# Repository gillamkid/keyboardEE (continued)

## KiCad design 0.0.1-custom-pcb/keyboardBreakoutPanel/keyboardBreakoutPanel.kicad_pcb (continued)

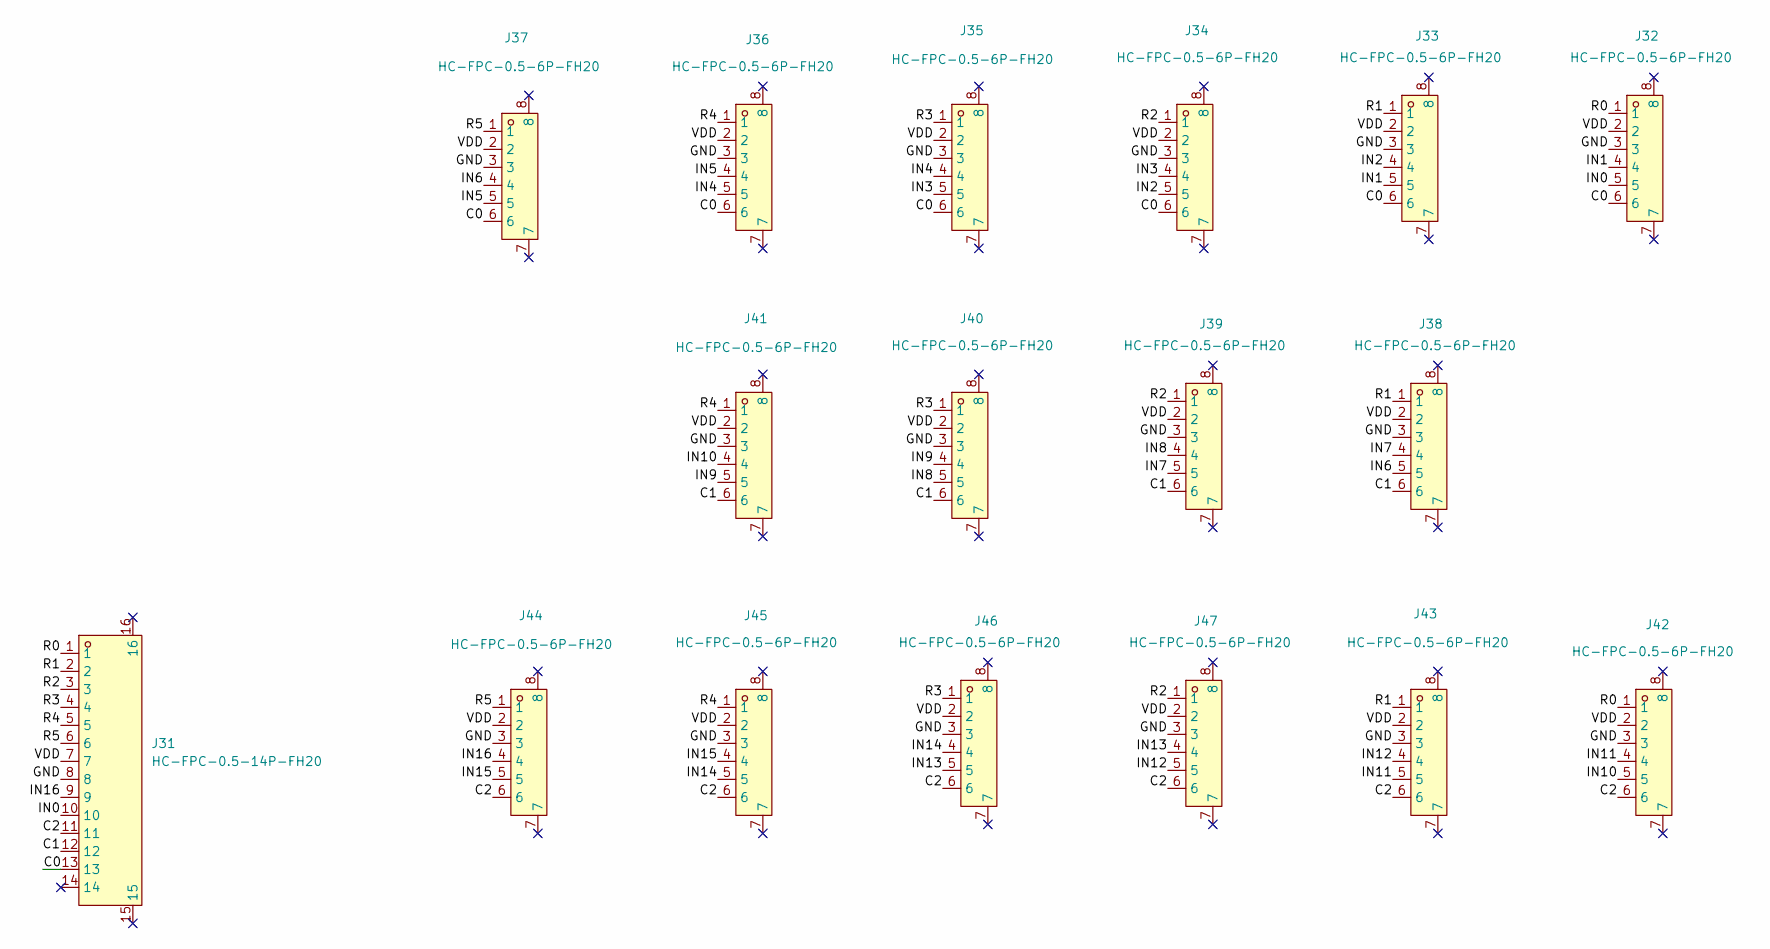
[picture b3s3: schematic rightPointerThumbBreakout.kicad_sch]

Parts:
J31: HC-FPC-0.5-14P-FH20; FPC-SMD_14P-P0.50_HC-FPC-0.5-14P-FH20; MPN HC-FPC-0.5-14P-FH20; LCSC Part C19273929
J32, J33, J34, J35, J36, J37, J38, J39, J40, J41, J42, J43, J44, J45, J46, J47: HC-FPC-0.5-6P-FH20; FPC-SMD_6P-P0.50_HC-FPC-0.5-6P-FH20; MPN HC-FPC-0.5-6P-FH20; LCSC Part C19273925

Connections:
/rightPointerThumbBreakout/C0: J31.13, J32.6, J33.6, J34.6, J35.6, J36.6, J37.6
/rightPointerThumbBreakout/C1: J31.12, J38.6, J39.6, J40.6, J41.6
/rightPointerThumbBreakout/C2: J31.11, J42.6, J43.6, J44.6, J45.6, J46.6, J47.6
/rightPointerThumbBreakout/GND: J31.8, J32.3, J33.3, J34.3, J35.3, J36.3, J37.3, J38.3, J39.3, J40.3, J41.3, J42.3, J43.3, J44.3, J45.3, J46.3, J47.3
/rightPointerThumbBreakout/IN0: J31.10, J32.5
/rightPointerThumbBreakout/IN1: J32.4, J33.5
/rightPointerThumbBreakout/IN2: J33.4, J34.5
/rightPointerThumbBreakout/IN3: J34.4, J35.5
/rightPointerThumbBreakout/IN4: J35.4, J36.5
/rightPointerThumbBreakout/IN5: J36.4, J37.5
/rightPointerThumbBreakout/IN6: J37.4, J38.5
/rightPointerThumbBreakout/IN7: J38.4, J39.5
/rightPointerThumbBreakout/IN8: J39.4, J40.5
/rightPointerThumbBreakout/IN9: J40.4, J41.5
/rightPointerThumbBreakout/IN10: J41.4, J42.5
/rightPointerThumbBreakout/IN11: J42.4, J43.5
/rightPointerThumbBreakout/IN12: J43.4, J47.5
/rightPointerThumbBreakout/IN13: J46.5, J47.4
/rightPointerThumbBreakout/IN14: J45.5, J46.4
/rightPointerThumbBreakout/IN15: J44.5, J45.4
/rightPointerThumbBreakout/IN16: J31.9, J44.4
/rightPointerThumbBreakout/R0: J31.1, J32.1, J42.1
/rightPointerThumbBreakout/R1: J31.2, J33.1, J38.1, J43.1
/rightPointerThumbBreakout/R2: J31.3, J34.1, J39.1, J47.1
/rightPointerThumbBreakout/R3: J31.4, J35.1, J40.1, J46.1
/rightPointerThumbBreakout/R4: J31.5, J36.1, J41.1, J45.1
/rightPointerThumbBreakout/R5: J31.6, J37.1, J44.1
/rightPointerThumbBreakout/VDD: J31.7, J32.2, J33.2, J34.2, J35.2, J36.2, J37.2, J38.2, J39.2, J40.2, J41.2, J42.2, J43.2, J44.2, J45.2, J46.2, J47.2

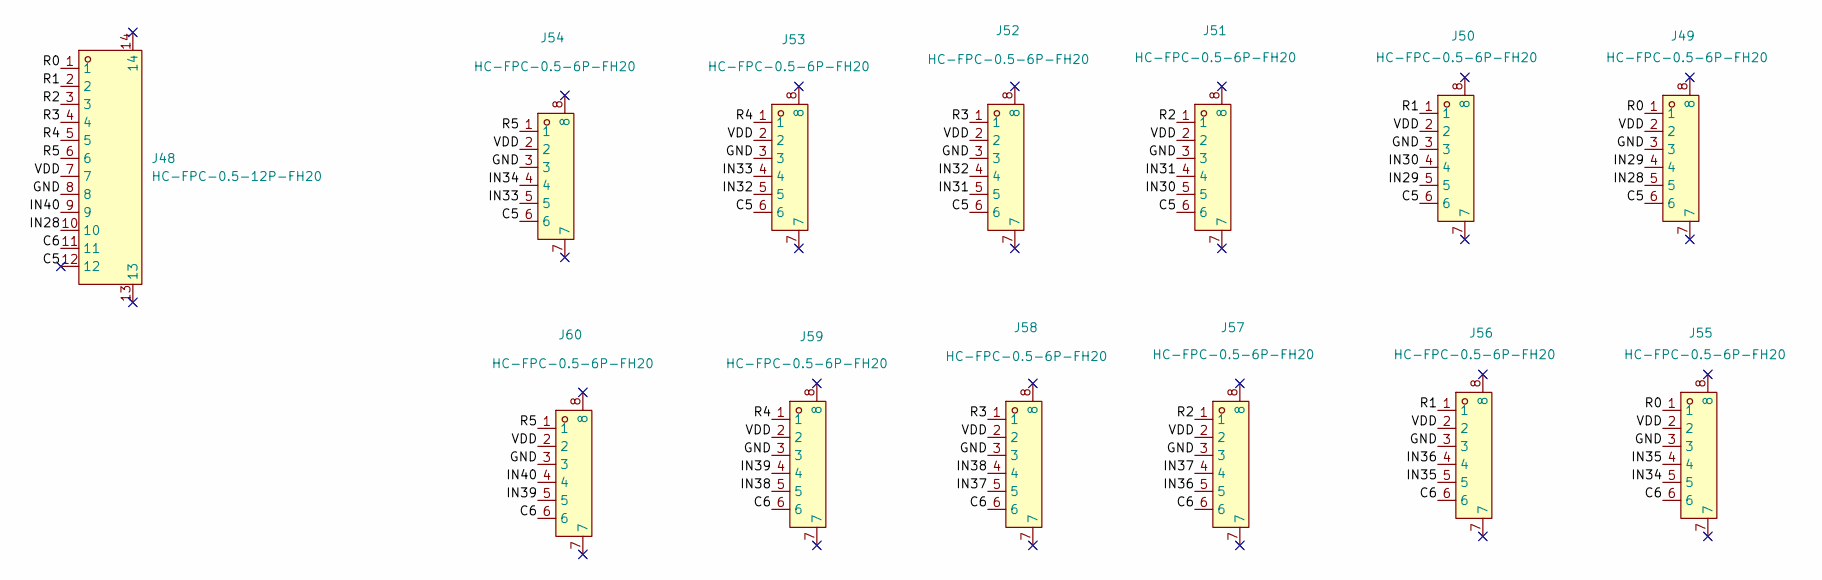
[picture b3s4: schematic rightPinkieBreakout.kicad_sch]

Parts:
J48: HC-FPC-0.5-12P-FH20; FPC-SMD_12P-P0.50_HC-FPC-0.5-12P-FH20; MPN HC-FPC-0.5-12P-FH20; LCSC Part C19273928
J49, J50, J51, J52, J53, J54, J55, J56, J57, J58, J59, J60: HC-FPC-0.5-6P-FH20; FPC-SMD_6P-P0.50_HC-FPC-0.5-6P-FH20; MPN HC-FPC-0.5-6P-FH20; LCSC Part C19273925

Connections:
/rightPinkieBreakout/C5: J48.12, J49.6, J50.6, J51.6, J52.6, J53.6, J54.6
/rightPinkieBreakout/C6: J48.11, J55.6, J56.6, J57.6, J58.6, J59.6, J60.6
/rightPinkieBreakout/GND: J48.8, J49.3, J50.3, J51.3, J52.3, J53.3, J54.3, J55.3, J56.3, J57.3, J58.3, J59.3, J60.3
/rightPinkieBreakout/IN28: J48.10, J49.5
/rightPinkieBreakout/IN29: J49.4, J50.5
/rightPinkieBreakout/IN30: J50.4, J51.5
/rightPinkieBreakout/IN31: J51.4, J52.5
/rightPinkieBreakout/IN32: J52.4, J53.5
/rightPinkieBreakout/IN33: J53.4, J54.5
/rightPinkieBreakout/IN34: J54.4, J55.5
/rightPinkieBreakout/IN35: J55.4, J56.5
/rightPinkieBreakout/IN36: J56.4, J57.5
/rightPinkieBreakout/IN37: J57.4, J58.5
/rightPinkieBreakout/IN38: J58.4, J59.5
/rightPinkieBreakout/IN39: J59.4, J60.5
/rightPinkieBreakout/IN40: J48.9, J60.4
/rightPinkieBreakout/R0: J48.1, J49.1, J55.1
/rightPinkieBreakout/R1: J48.2, J50.1, J56.1
/rightPinkieBreakout/R2: J48.3, J51.1, J57.1
/rightPinkieBreakout/R3: J48.4, J52.1, J58.1
/rightPinkieBreakout/R4: J48.5, J53.1, J59.1
/rightPinkieBreakout/R5: J48.6, J54.1, J60.1
/rightPinkieBreakout/VDD: J48.7, J49.2, J50.2, J51.2, J52.2, J53.2, J54.2, J55.2, J56.2, J57.2, J58.2, J59.2, J60.2

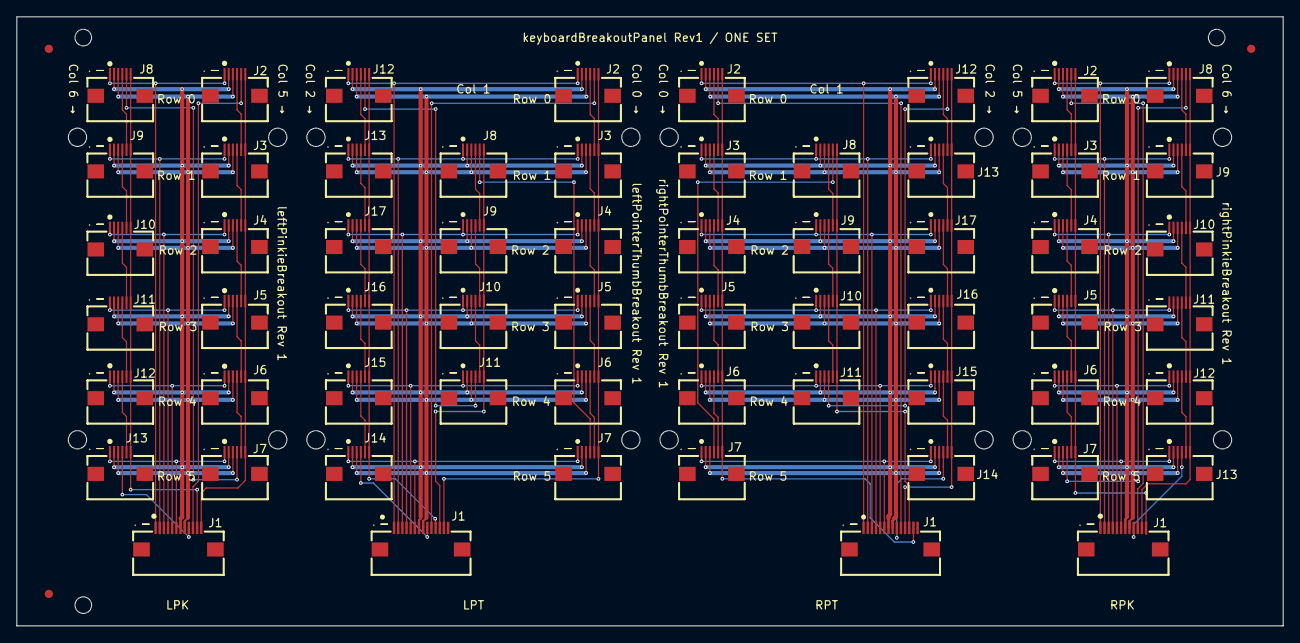
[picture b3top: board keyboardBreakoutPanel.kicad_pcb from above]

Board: 2 copper layers, 152.4 x 73.3 mm, 82 parts (0 on the bottom side), 102 nets.

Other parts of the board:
FID1, FID2, FID3: Fiducial; Fiducial_1mm
H1, H2, H3, H4, H5, H6, H7, H8, H9, H10, H11, H12, H13, H14, H15, H16: MountingHole_2.2mm_M2_4.4mmHead
TOOL1, TOOL2, TOOL3: Tooling hole; ToolingHole_2mm

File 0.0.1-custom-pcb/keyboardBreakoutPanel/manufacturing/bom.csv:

Comment,Designator,Footprint,LCSC,Quantity
HC-FPC-0.5-12P-FH20,"J1,J48",FPC-SMD_12P-P0.50_HC-FPC-0.5-12P-FH20,C19273928,2
HC-FPC-0.5-6P-FH20,"J2,J3,J4,J5,J6,J7,J8,J9,J10,J11,J12,J13,J15,J16,J17,J18,J19,J20,J21,J22,J23,J24,J25,J26,J27,J28,J29,J30,J32,J33,J34,J35,J36,J37,J38,J39,J40,J41,J42,J43,J44,J45,J46,J47,J49,J50,J51,J52,J53,J54,J55,J56,J57,J58,J59,J60",FPC-SMD_6P-P0.50_HC-FPC-0.5-6P-FH20,C19273925,56
HC-FPC-0.5-14P-FH20,"J14,J31",FPC-SMD_14P-P0.50_HC-FPC-0.5-14P-FH20,C19273929,2

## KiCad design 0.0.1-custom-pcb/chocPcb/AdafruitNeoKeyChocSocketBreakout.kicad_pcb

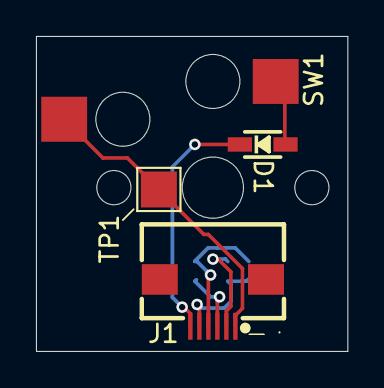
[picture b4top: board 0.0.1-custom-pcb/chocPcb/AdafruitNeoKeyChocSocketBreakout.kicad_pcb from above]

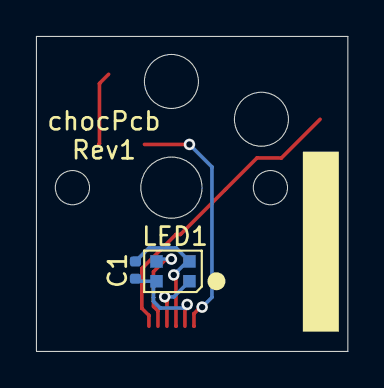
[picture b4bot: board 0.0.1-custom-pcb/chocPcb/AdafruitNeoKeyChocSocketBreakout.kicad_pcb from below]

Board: 2 copper layers, 17.3 x 17.5 mm, 6 parts (2 on the bottom side), 7 nets.

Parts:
C1: 100nF; C_0402_1005Metric
D1: 1N4148WS; SOD-323
J1: HC-FPC-0.5-6P-FH20; FPC-SMD_6P-P0.50_HC-FPC-0.5-6P-FH20
LED1: WS2812B-2020; LED_WS2812B-2020_PLCC4_2.0x2.0mm
SW1: Kailh Choc socket; KAILH_CHOC_SOCKET
TP1: TestPoint_Pad_2.0x2.0mm

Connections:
GND: C1.2, J1.4, LED1.2
unnamed: D1.A, SW1.1
NEO_IN: J1.2, LED1.3
NEO_OUT: J1.3, LED1.1
SWITCHA: J1.1, SW1.2, TP1.1
SWITCHC: D1.C, J1.6
VDD: C1.1, J1.5, LED1.4

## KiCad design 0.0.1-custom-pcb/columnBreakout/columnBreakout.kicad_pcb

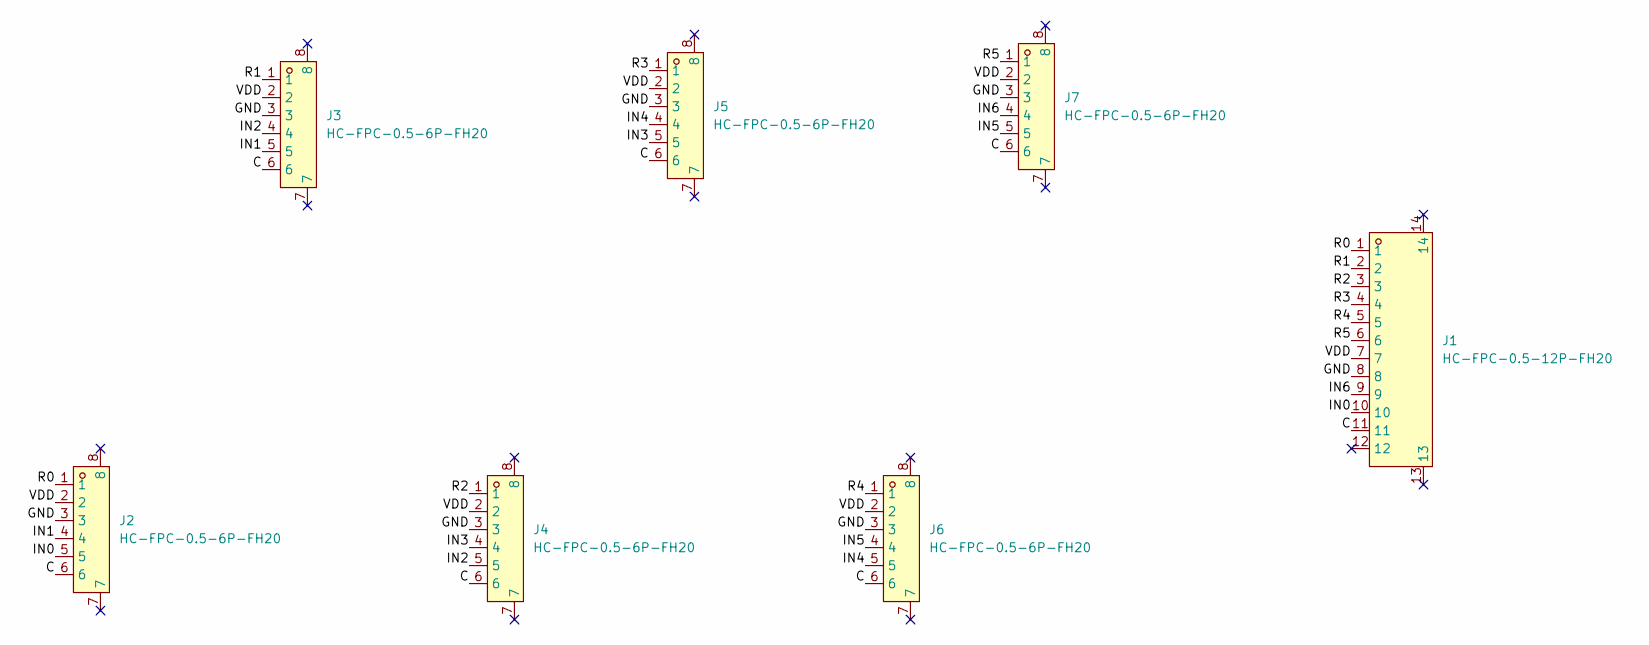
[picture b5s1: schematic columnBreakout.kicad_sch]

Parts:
J1: HC-FPC-0.5-12P-FH20; FPC-SMD_12P-P0.50_HC-FPC-0.5-12P-FH20; MPN HC-FPC-0.5-12P-FH20; LCSC Part C19273928
J2, J3, J4, J5, J6, J7: HC-FPC-0.5-6P-FH20; FPC-SMD_6P-P0.50_HC-FPC-0.5-6P-FH20; MPN HC-FPC-0.5-6P-FH20; LCSC Part C19273925

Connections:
/C: J1.11 (R1), J2.6 (VDD), J3.6 (VDD), J4.6 (VDD), J5.6 (VDD), J6.6 (VDD), J7.6 (VDD)
/GND: J1.8 (R4), J2.3 (IN0), J3.3 (IN1), J4.3 (IN2), J5.3 (IN3), J6.3 (IN4), J7.3 (IN5)
/IN0: J1.10 (R2), J2.5 (GND)
/IN1: J2.4 (IN1), J3.5 (GND)
/IN2: J3.4 (IN2), J4.5 (GND)
/IN3: J4.4 (IN3), J5.5 (GND)
/IN4: J5.4 (IN4), J6.5 (GND)
/IN5: J6.4 (IN5), J7.5 (GND)
/IN6: J1.9 (R3), J7.4 (IN6)
/R0: J1.1, J2.1 (R0)
/R1: J1.2 (C), J3.1 (R1)
/R2: J1.3 (IN0), J4.1 (R2)
/R3: J1.4 (IN6), J5.1 (R3)
/R4: J1.5 (GND), J6.1 (R4)
/R5: J1.6 (VDD), J7.1 (R5)
/VDD: J1.7 (R5), J2.2 (C), J3.2 (C), J4.2 (C), J5.2 (C), J6.2 (C), J7.2 (C)

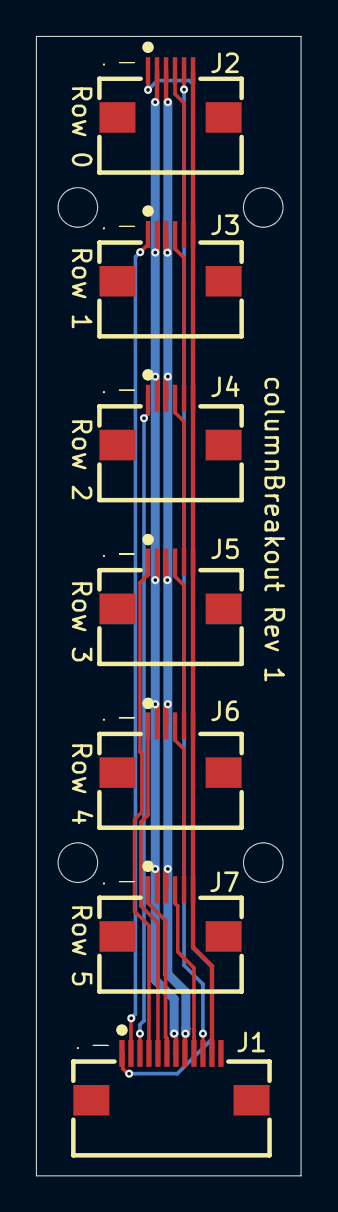
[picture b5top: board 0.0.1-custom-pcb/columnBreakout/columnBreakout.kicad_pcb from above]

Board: 2 copper layers, 14.7 x 63.3 mm, 11 parts (0 on the bottom side), 16 nets.

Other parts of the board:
H1, H2, H3, H4: MountingHole_2.2mm_M2_4.4mmHead

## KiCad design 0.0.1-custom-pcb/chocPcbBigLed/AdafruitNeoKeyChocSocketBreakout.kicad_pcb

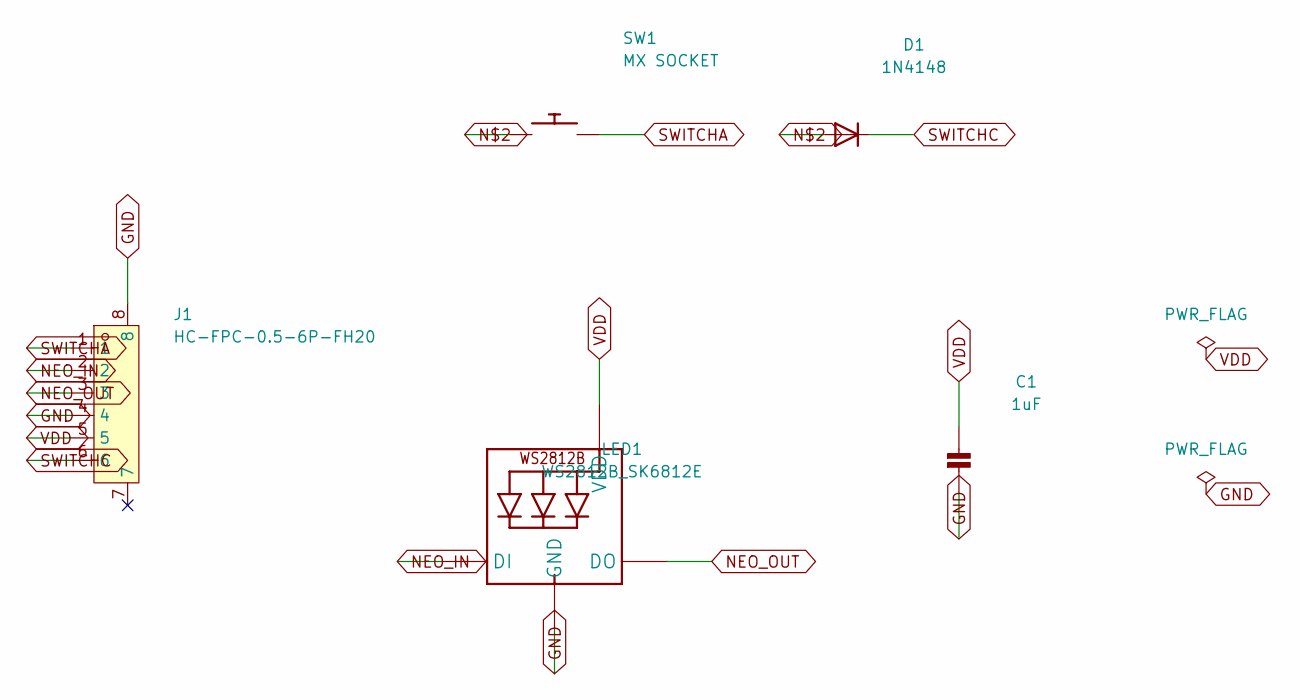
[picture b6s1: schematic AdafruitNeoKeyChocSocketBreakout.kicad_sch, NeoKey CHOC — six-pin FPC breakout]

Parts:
C1: 1uF; 0603-NO
D1: 1N4148; SOD-323
J1: HC-FPC-0.5-6P-FH20; FPC-SMD_6P-P0.50_HC-FPC-0.5-6P-FH20; MPN HC-FPC-0.5-6P-FH20; LCSC Part C19273925
LED1: WS2812B_SK6812E; NEO3535_REVERSE
SW1: MX SOCKET; KAILH_CHOC_SOCKET

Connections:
GND: C1.2, J1.4, J1.8, LED1.3-GND (GND)
unnamed: D1.A, SW1.1
NEO_IN: J1.2, LED1.4-DIN (DI)
NEO_OUT: J1.3, LED1.2-DOUT (DO)
SWITCHA: J1.1, SW1.2
SWITCHC: D1.C, J1.6, J1.7
VDD: C1.1, J1.5, LED1.1-VDD (VDD)

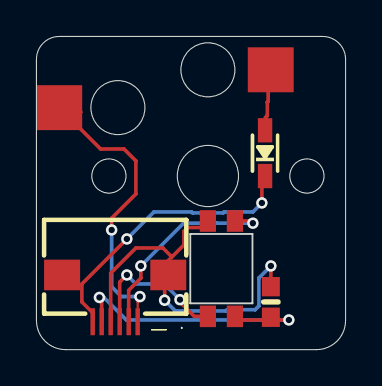
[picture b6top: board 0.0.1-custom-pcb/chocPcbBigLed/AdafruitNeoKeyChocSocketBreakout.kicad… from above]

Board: 2 copper layers, 17.2 x 17.4 mm, 5 parts (0 on the bottom side), 7 nets.

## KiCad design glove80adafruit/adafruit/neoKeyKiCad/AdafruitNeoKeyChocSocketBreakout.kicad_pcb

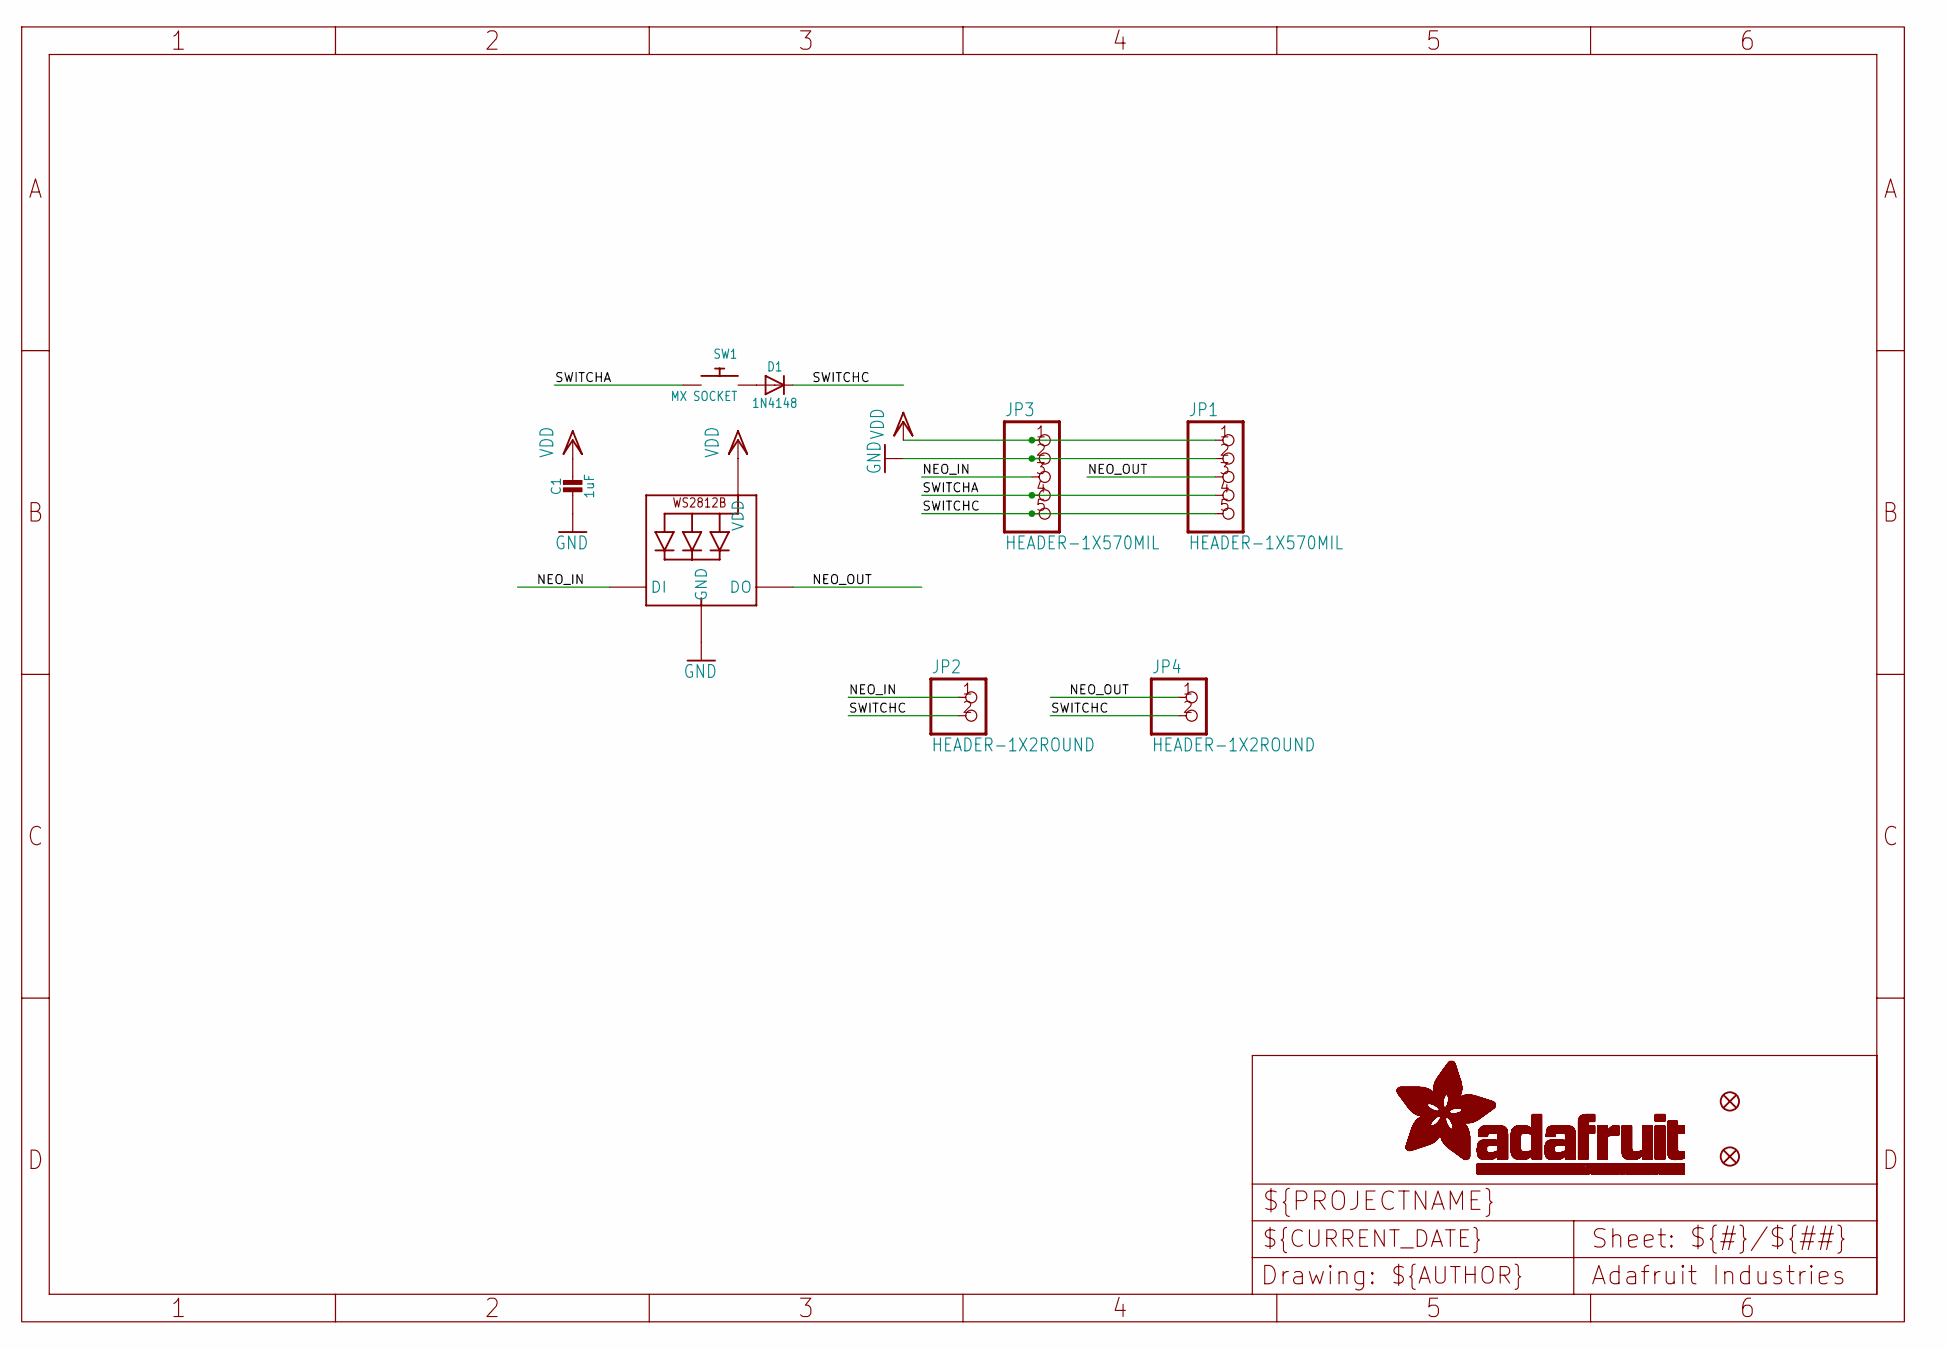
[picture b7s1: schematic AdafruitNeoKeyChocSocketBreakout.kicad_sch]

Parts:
C1: 1uF; 0603-NO
D1: 1N4148; SOD-323
FID3, FID4: FIDUCIAL_1MM
JP1, JP3: HEADER-1X570MIL; 1X05_ROUND_70
JP2, JP4: HEADER-1X2ROUND; 1X02_ROUND
LED1: WS2812B_SK6812E; NEO3535_REVERSE
SW1: MX SOCKET; KAILH_CHOC_SOCKET

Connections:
GND: C1.2, JP1.2, JP3.2, LED1.3-GND (GND)
unnamed: D1.A, SW1.1
NEO_IN: JP2.1, JP3.3, LED1.4-DIN (DI)
NEO_OUT: JP1.3, JP4.1, LED1.2-DOUT (DO)
SWITCHA: JP1.4, JP3.4, SW1.2
SWITCHC: D1.C, JP1.5, JP2.2, JP3.5, JP4.2
VDD: C1.1, JP1.1, JP3.1, LED1.1-VDD (VDD)

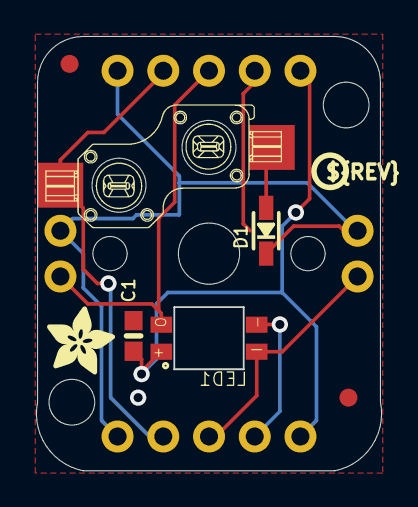
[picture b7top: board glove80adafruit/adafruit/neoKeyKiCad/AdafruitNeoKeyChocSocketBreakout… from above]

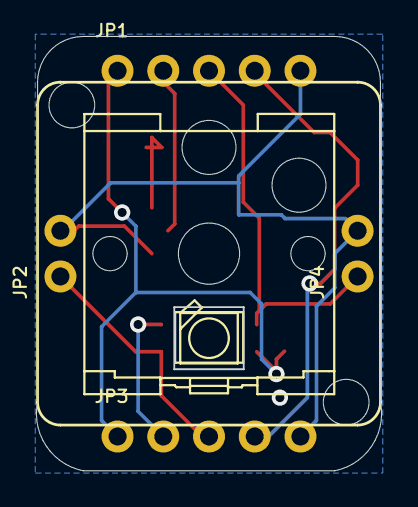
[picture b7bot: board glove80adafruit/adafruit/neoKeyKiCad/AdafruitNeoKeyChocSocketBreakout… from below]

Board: 2 copper layers, 19.2 x 24.1 mm, 39 parts (14 on the bottom side), 7 nets.

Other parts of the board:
PLABEL0, PLABEL20: PLABEL0
PLABEL1: PLABEL1
PLABEL2: PLABEL2
PLABEL3: PLABEL3
PLABEL4: PLABEL4
PLABEL5: PLABEL5
PLABEL6, PLABEL21: PLABEL6
PLABEL7: PLABEL7
PLABEL8, PLABEL22: PLABEL8
PLABEL9, PLABEL23: PLABEL9
PLABEL10: PLABEL10
PLABEL11: PLABEL11
PLABEL12: PLABEL12
PLABEL13: PLABEL13
PLABEL14: PLABEL14
PLABEL15: PLABEL15
PLABEL16: PLABEL16
PLABEL17: PLABEL17
PLABEL18: PLABEL18
PLABEL19: PLABEL19
PLABEL200: PLABEL200
U$1: PCBFEAT-REV-040
U$2: ADAFRUIT_3.5MM
UNK_HOLE_0: dummyfp0
UNK_HOLE_1: dummyfp1
